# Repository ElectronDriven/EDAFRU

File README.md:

# EDAFRU
Electron Driven Air to Fuel Ratio Measurement Unit

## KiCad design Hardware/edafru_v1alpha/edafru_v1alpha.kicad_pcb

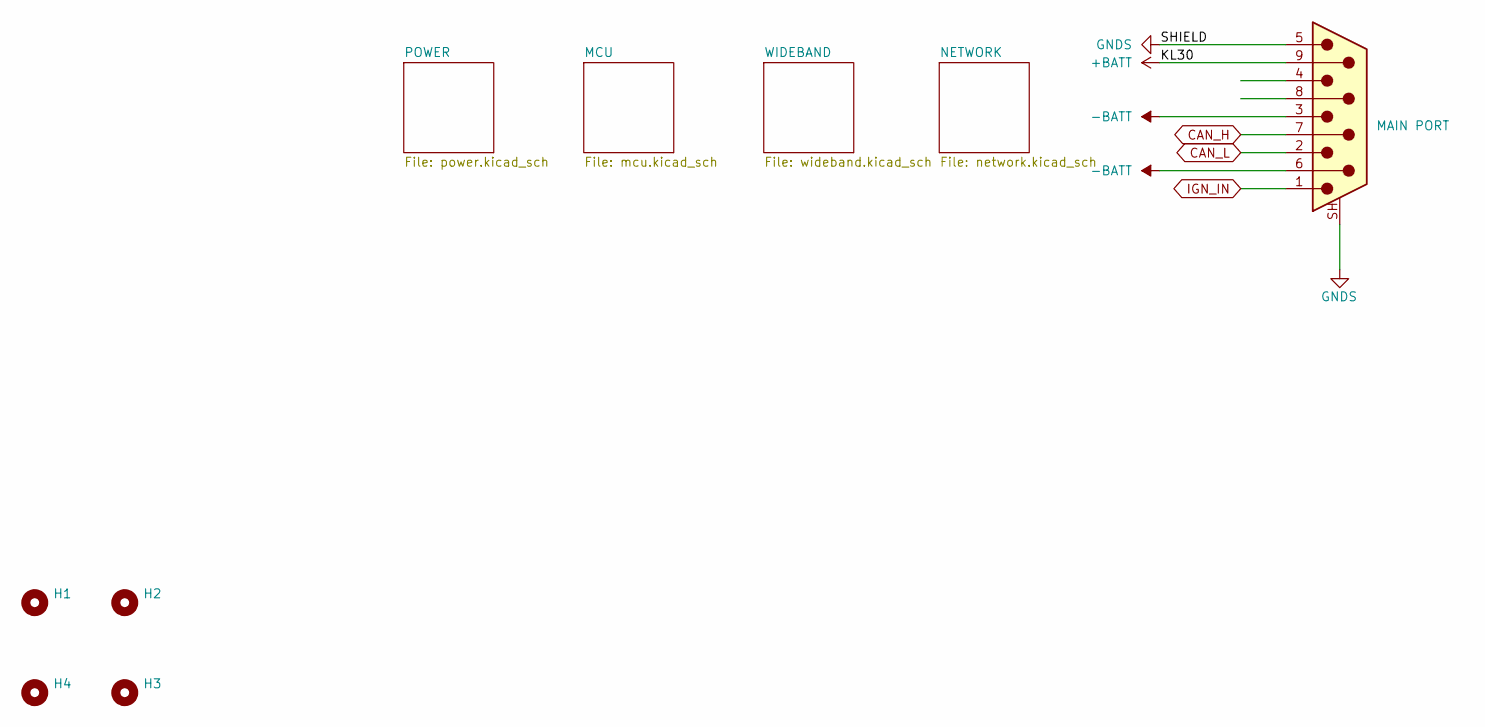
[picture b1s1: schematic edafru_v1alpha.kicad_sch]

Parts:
H1, H2, H3, H4: MountingHole; MountingHole_3.2mm_M3_DIN965
J2: MAIN PORT; DSUB-9_Pins_Horizontal_P2.77x2.84mm_EdgePinOffset4.94mm_Hou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

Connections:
+BATT: J2.9; also elsewhere on the board
-BATT: J2.3, J2.6; also elsewhere on the board
CAN_H: J2.7; also elsewhere on the board
CAN_L: J2.2; also elsewhere on the board
GNDS: J2.5, J2.SH (PAD)
IGN_IN: J2.1; also elsewhere on the board

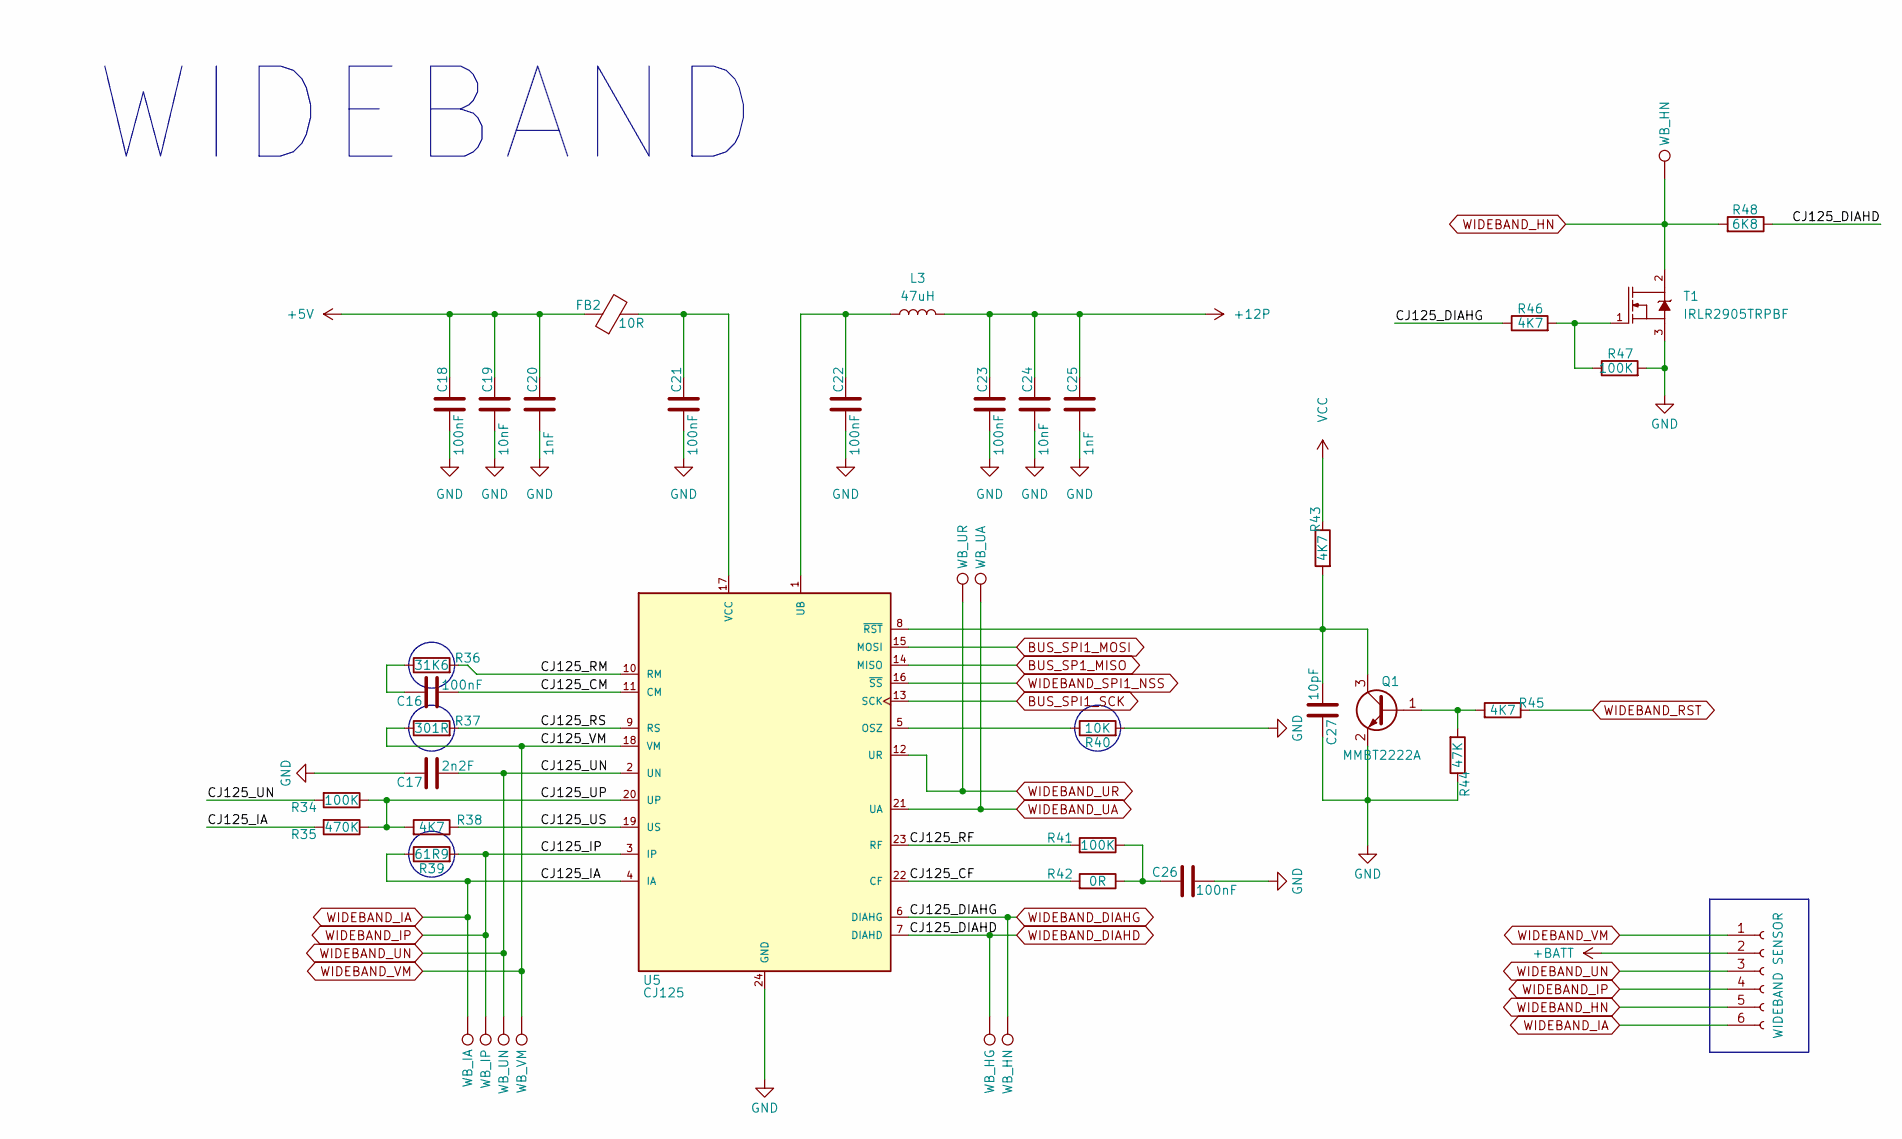
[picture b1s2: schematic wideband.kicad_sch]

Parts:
C16, C26: 100nF; C_0603_1608Metric_Pad1.08x0.95mm_HandSolder
C17: 2n2F; C_0603_1608Metric_Pad1.08x0.95mm_HandSolder
C18, C21, C22, C23: 100nF; C_1206_3216Metric_Pad1.33x1.80mm_HandSolder
C19, C24: 10nF; C_1206_3216Metric_Pad1.33x1.80mm_HandSolder
C20, C25: 1nF; C_1206_3216Metric_Pad1.33x1.80mm_HandSolder
C27: 10pF; C_0603_1608Metric_Pad1.08x0.95mm_HandSolder
FB2: 10R; L_1206_3216Metric_Pad1.22x1.90mm_HandSolder
J4: WIDEBAND SENSOR; Molex_KK-254_AE-6410-06A_1x06_P2.54mm_Vertical
L3: 47uH; L_1210_3225Metric_Pad1.42x2.65mm_HandSolder
Q1: MMBT2222A; SOT-23
R34, R41: 100K; R_0603_1608Metric_Pad0.98x0.95mm_HandSolder
R35: 470K; R_0603_1608Metric_Pad0.98x0.95mm_HandSolder
R36: 31K6; R_MELF_MMB-0207
R37: 301R; R_MELF_MMB-0207
R38, R43, R45: 4K7; R_0603_1608Metric_Pad0.98x0.95mm_HandSolder
R39: 61R9; R_MELF_MMB-0207
R40: 10K; R_MELF_MMB-0207
R42: 0R; R_0603_1608Metric_Pad0.98x0.95mm_HandSolder
R44: 47K; R_0603_1608Metric_Pad0.98x0.95mm_HandSolder
R46: 4K7; R_1206_3216Metric_Pad1.30x1.75mm_HandSolder
R47: 100K; R_1206_3216Metric_Pad1.30x1.75mm_HandSolder
R48: 6K8; R_1206_3216Metric_Pad1.30x1.75mm_HandSolder
T1: IRLR2905TRPBF
TP1: WB_IA; TestPoint_Pad_D1.0mm
TP2: WB_IP; TestPoint_Pad_D1.0mm
TP3: WB_UN; TestPoint_Pad_D1.0mm
TP4: WB_VM; TestPoint_Pad_D1.0mm
TP5: WB_UR; TestPoint_Pad_D1.0mm
TP6: WB_UA; TestPoint_Pad_D1.0mm
TP7: WB_HG; TestPoint_Pad_D1.0mm
TP8, TP9: WB_HN; TestPoint_Pad_D1.0mm
U5: CJ125; SOIC-24W_7.5x15.4mm_P1.27mm

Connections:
+5V: C18.1, C19.1, C20.1, FB2.1; also elsewhere on the board
+12P: C23.1, C24.1, C25.1, L3.2; also elsewhere on the board
+BATT: J4.2; also elsewhere on the board
/WIDEBAND/CJ125_CF: R42.2, U5.22 (CF)
/WIDEBAND/CJ125_CM: C16.1, U5.11 (CM)
/WIDEBAND/CJ125_RF: R41.2, U5.23 (RF)
/WIDEBAND/CJ125_RM: R36.2, U5.10 (RM)
/WIDEBAND/CJ125_RS: R37.2, U5.9 (RS)
/WIDEBAND/CJ125_UP: R34.1, R35.1, R38.2, U5.20 (UP)
/WIDEBAND/CJ125_US: R38.1, U5.19 (US)
BUS_SP1_MISO: U5.14 (MISO); also elsewhere on the board
BUS_SPI1_MOSI: U5.15 (MOSI); also elsewhere on the board
BUS_SPI1_SCK: U5.13 (SCK); also elsewhere on the board
GND: C17.2, C18.2, C19.2, C20.2, C21.2, C22.2, C23.2, C24.2, C25.2, C26.2, C27.2, Q1.2 (E), R40.2, R44.1, R47.2, T1.3, U5.24 (GND); also elsewhere on the board
unnamed: C16.2, R36.1
unnamed: C26.1, R41.1, R42.1
unnamed: Q1.1 (B), R44.2, R45.2
unnamed: C27.1, Q1.3 (C), R43.2, U5.8 (~RST)
unnamed: R46.2, R47.1, T1.1
unnamed: R40.1, U5.5 (OSZ)
unnamed: C22.1, L3.1, U5.1 (UB)
unnamed: C21.1, FB2.2, U5.17 (VCC)
VCC: R43.1; also elsewhere on the board
WIDEBAND_DIAHD: R48.1, TP7.1 (1_1), U5.7 (DIAHD); also elsewhere on the board
WIDEBAND_DIAHG: R46.1, TP8.1 (1_1), U5.6 (DIAHG); also elsewhere on the board
WIDEBAND_HN: J4.5, R48.2, T1.2, T1.PAD, TP9.1 (1_1)
WIDEBAND_IA: J4.6, R35.2, R39.1, TP1.1 (1_1), U5.4 (IA)
WIDEBAND_IP: J4.4, R39.2, TP2.1 (1_1), U5.3 (IP)
WIDEBAND_RST: R45.1; also elsewhere on the board
WIDEBAND_SPI1_NSS: U5.16 (~SS); also elsewhere on the board
WIDEBAND_UA: TP6.1 (1_1), U5.21 (UA); also elsewhere on the board
WIDEBAND_UN: C17.1, J4.3, R34.2, TP3.1 (1_1), U5.2 (UN)
WIDEBAND_UR: TP5.1 (1_1), U5.12 (UR); also elsewhere on the board
WIDEBAND_VM: J4.1, R37.1, TP4.1 (1_1), U5.18 (VM)

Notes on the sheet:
WIDEBAND

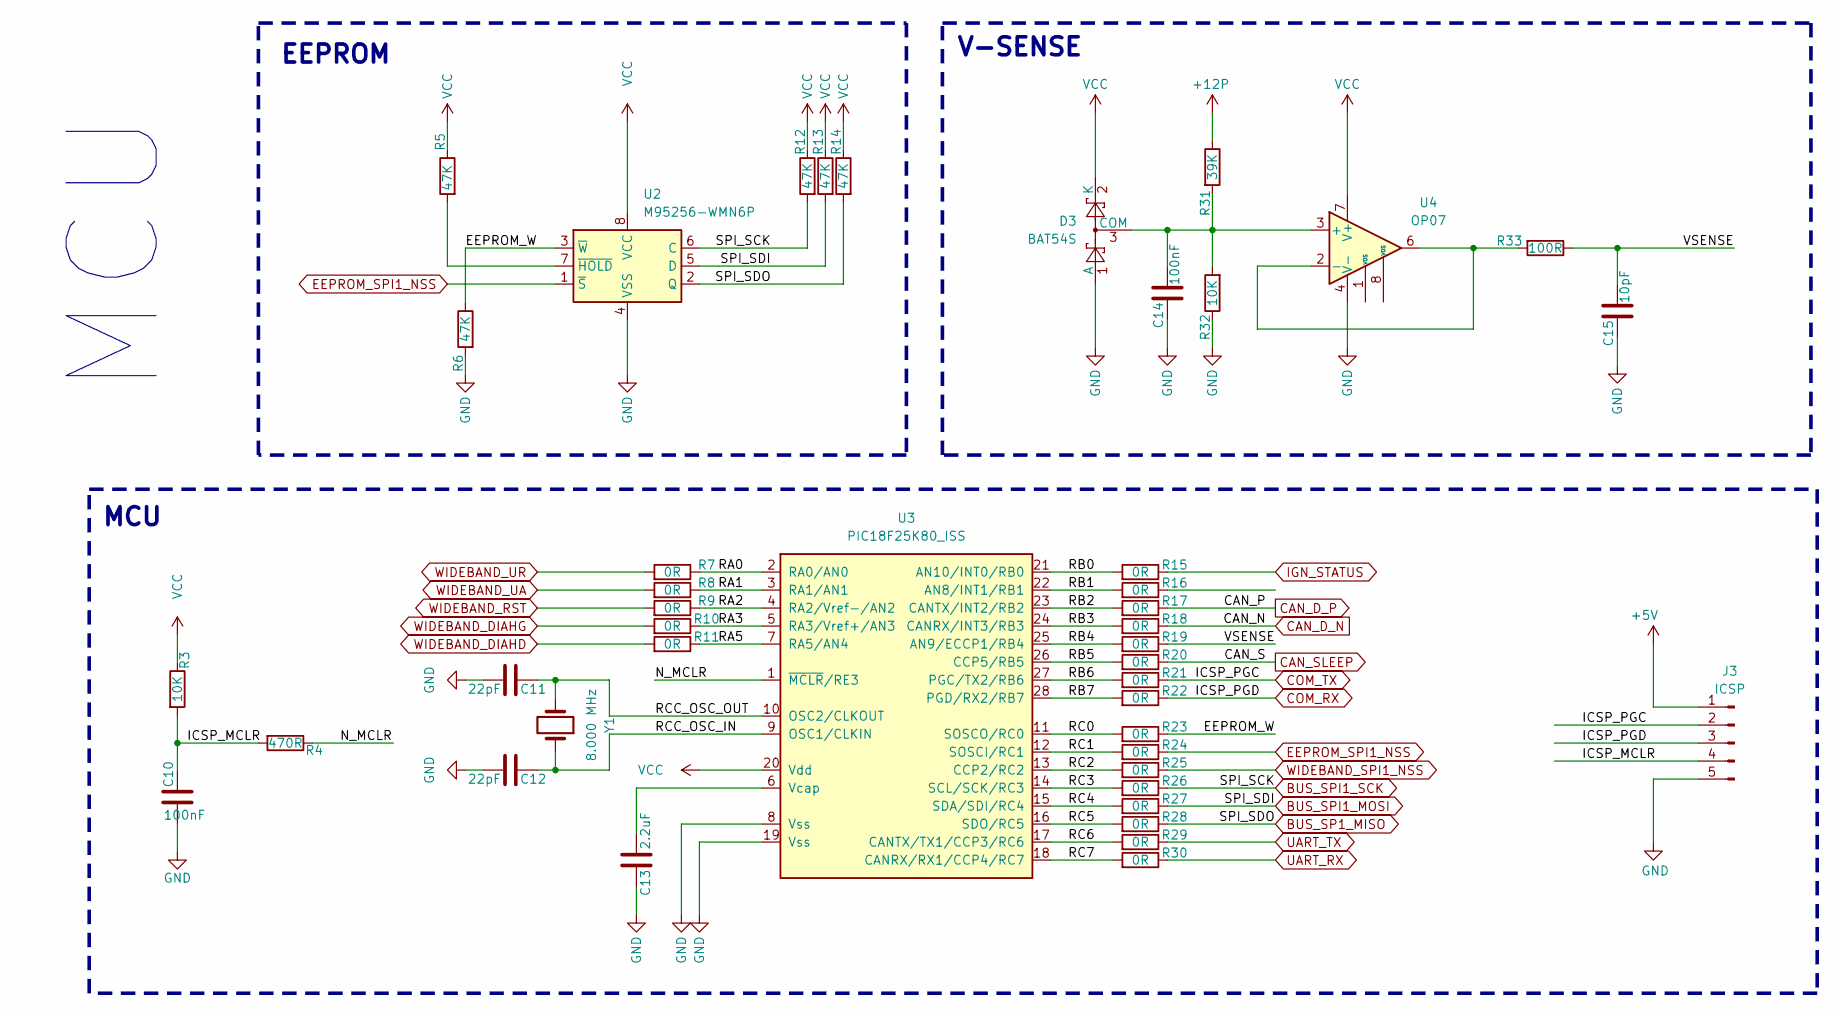
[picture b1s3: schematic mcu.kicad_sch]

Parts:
C10, C14: 100nF; C_0603_1608Metric_Pad1.08x0.95mm_HandSolder
C11, C12: 22pF; C_0603_1608Metric_Pad1.08x0.95mm_HandSolder
C13: 2.2uF; C_0603_1608Metric_Pad1.08x0.95mm_HandSolder
C15: 10pF; C_0603_1608Metric_Pad1.08x0.95mm_HandSolder
D3: BAT54S; SOT-23
J3: ICSP; PinHeader_1x05_P2.54mm_Vertical
R3, R32: 10K; R_0603_1608Metric_Pad0.98x0.95mm_HandSolder
R4: 470R; R_0603_1608Metric_Pad0.98x0.95mm_HandSolder
R5, R6, R12, R13, R14: 47K; R_0603_1608Metric_Pad0.98x0.95mm_HandSolder
R7, R8, R9, R10, R11, R15, R16, R17, R18, R19, R20, R21, R22, R23, R24, R25, R26, R27, R28, R29, R30: 0R; R_0603_1608Metric_Pad0.98x0.95mm_HandSolder
R31: 39K; R_0603_1608Metric_Pad0.98x0.95mm_HandSolder
R33: 100R; R_0603_1608Metric_Pad0.98x0.95mm_HandSolder
U2: M95256-WMN6P; SOIC-8_3.9x4.9mm_P1.27mm
U3: PIC18F25K80_ISS; SSOP-28_5.3x10.2mm_P0.65mm
U4: OP07; SOIC-8_3.9x4.9mm_P1.27mm
Y1: 8.000 MHz; Crystal_SMD_5032-2Pin_5.0x3.2mm_HandSoldering

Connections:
+5V: J3.1; also elsewhere on the board
+12P: R31.1; also elsewhere on the board
/MCU/EEPROM_W: R6.1, R23.1, U2.3 (~W)
/MCU/ICSP_MCLR: C10.1, J3.4, R3.2, R4.2
/MCU/N_MCLR: R4.1, U3.1 (~MCLR/RE3)
/MCU/RA0: R7.1, U3.2 (RA0/AN0)
/MCU/RA1: R8.1, U3.3 (RA1/AN1)
/MCU/RA2: R9.1, U3.4 (RA2/Vref-/AN2)
/MCU/RA3: R10.1, U3.5 (RA3/Vref+/AN3)
/MCU/RA5: R11.1, U3.7 (RA5/AN4)
/MCU/RB0: R15.2, U3.21 (AN10/INT0/RB0)
/MCU/RB1: R16.2, U3.22 (AN8/INT1/RB1)
/MCU/RB2: R17.2, U3.23 (CANTX/INT2/RB2)
/MCU/RB3: R18.2, U3.24 (CANRX/INT3/RB3)
/MCU/RB4: R19.2, U3.25 (AN9/ECCP1/RB4)
/MCU/RB5: R20.2, U3.26 (CCP5/RB5)
/MCU/RB6: R21.2, U3.27 (PGC/TX2/RB6)
/MCU/RB7: R22.2, U3.28 (PGD/RX2/RB7)
/MCU/RC0: R23.2, U3.11 (SOSCO/RC0)
/MCU/RC1: R24.2, U3.12 (SOSCI/RC1)
/MCU/RC2: R25.2, U3.13 (CCP2/RC2)
/MCU/RC3: R26.2, U3.14 (SCL/SCK/RC3)
/MCU/RC4: R27.2, U3.15 (SDA/SDI/RC4)
/MCU/RC5: R28.2, U3.16 (SDO/RC5)
/MCU/RC6: R29.2, U3.17 (CANTX/TX1/CCP3/RC6)
/MCU/RC7: R30.2, U3.18 (CANRX/RX1/CCP4/RC7)
/MCU/RCC_OSC_IN: C12.1, U3.9 (OSC1/CLKIN), Y1.1
/MCU/RCC_OSC_OUT: C11.1, U3.10 (OSC2/CLKOUT), Y1.2
/MCU/VSENSE: C15.1, R19.1, R33.1
BUS_SP1_MISO: R14.2, R28.1, U2.2 (Q); also elsewhere on the board
BUS_SPI1_MOSI: R13.2, R27.1, U2.5 (D); also elsewhere on the board
BUS_SPI1_SCK: R12.2, R26.1, U2.6 (C); also elsewhere on the board
CAN_D_N: R18.1; also elsewhere on the board
CAN_D_P: R17.1; also elsewhere on the board
CAN_SLEEP: R20.1; also elsewhere on the board
COM_RX: J3.3, R22.1
COM_TX: J3.2, R21.1
EEPROM_SPI1_NSS: R24.1, U2.1 (~S)
GND: C10.2, C11.2, C12.2, C13.1, C14.2, C15.2, D3.1 (A), J3.5, R6.2, R32.1, U2.4 (VSS), U3.8 (Vss), U3.19 (Vss), U4.4 (V-); also elsewhere on the board
IGN_STATUS: R15.1; also elsewhere on the board
unnamed: C14.1, D3.3 (COM), R31.2, R32.2, U4.3 (+)
unnamed: R5.2, U2.7 (~HOLD)
unnamed: C13.2, U3.6 (Vcap)
unnamed: R33.2, U4.2 (-), U4.6
UART_RX: R30.1
UART_TX: R29.1
VCC: D3.2 (K), R3.1, R5.1, R12.1, R13.1, R14.1, U2.8 (VCC), U3.20 (Vdd), U4.7 (V+); also elsewhere on the board
WIDEBAND_DIAHD: R11.2; also elsewhere on the board
WIDEBAND_DIAHG: R10.2; also elsewhere on the board
WIDEBAND_RST: R9.2; also elsewhere on the board
WIDEBAND_SPI1_NSS: R25.1; also elsewhere on the board
WIDEBAND_UA: R8.2; also elsewhere on the board
WIDEBAND_UR: R7.2; also elsewhere on the board

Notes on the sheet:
EEPROM
V-SENSE
MCU
MCU

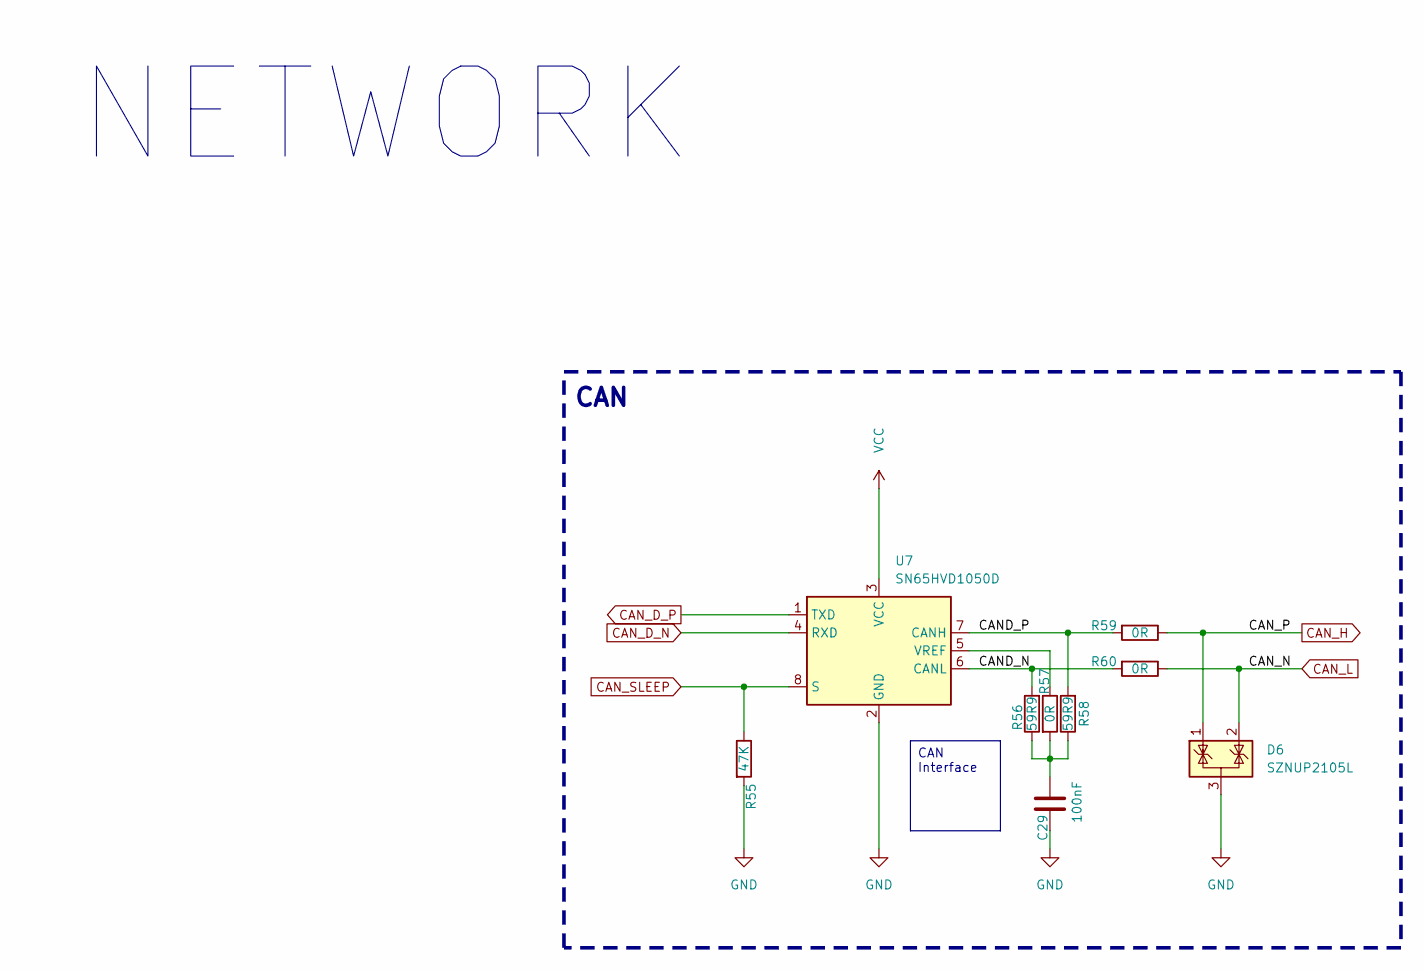
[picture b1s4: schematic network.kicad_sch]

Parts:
C29: 100nF; C_0603_1608Metric_Pad1.08x0.95mm_HandSolder
D6: SZNUP2105L; SOT-23
R55: 47K; R_0603_1608Metric_Pad0.98x0.95mm_HandSolder
R56, R58: 59R9; R_0603_1608Metric_Pad0.98x0.95mm_HandSolder
R57, R59, R60: 0R; R_0603_1608Metric_Pad0.98x0.95mm_HandSolder
U7: SN65HVD1050D; SOIC-8_3.9x4.9mm_P1.27mm

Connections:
/NETWORK/CAND_N: R56.2, R60.2, U7.6 (CANL)
/NETWORK/CAND_P: R58.2, R59.2, U7.7 (CANH)
CAN_D_N: U7.4 (RXD); also elsewhere on the board
CAN_D_P: U7.1 (TXD); also elsewhere on the board
CAN_H: D6.1 (K), R59.1; also elsewhere on the board
CAN_L: D6.2 (K), R60.1; also elsewhere on the board
CAN_SLEEP: R55.1, U7.8 (S); also elsewhere on the board
GND: C29.2, D6.3 (A), R55.2, U7.2 (GND); also elsewhere on the board
unnamed: C29.1, R56.1, R57.2, R58.1
unnamed: R57.1, U7.5 (VREF)
VCC: U7.3 (VCC); also elsewhere on the board

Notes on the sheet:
CAN
NETWORK
CAN Interface

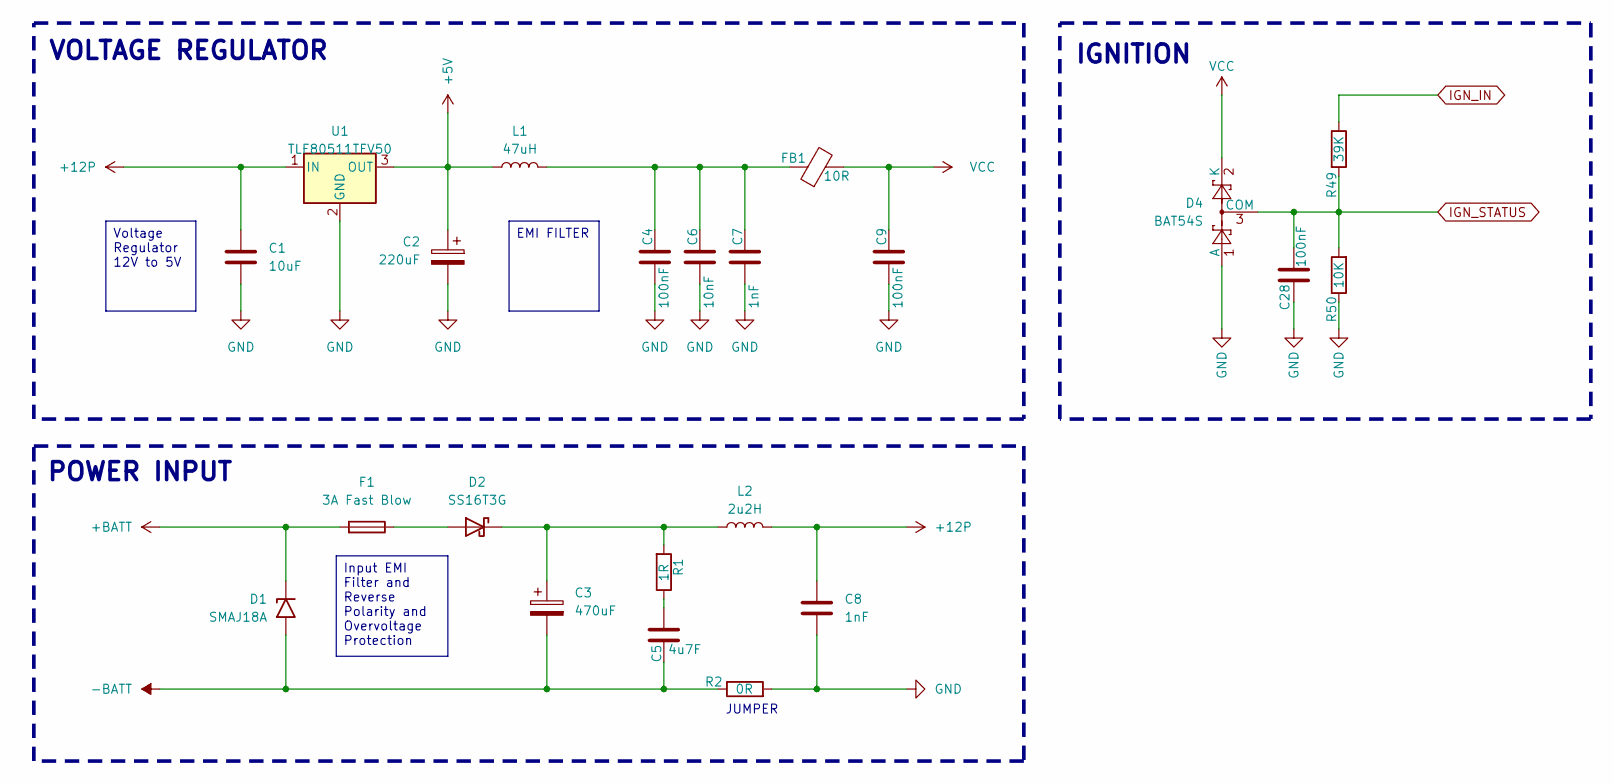
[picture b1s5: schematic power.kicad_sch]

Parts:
C1: 10uF; C_1206_3216Metric_Pad1.33x1.80mm_HandSolder
C2: 220uF; CP_EIA-7343-30_AVX-N
C3: 470uF; CP_Elec_10x10
C4, C9: 100nF; C_1206_3216Metric_Pad1.33x1.80mm_HandSolder
C5: 4u7F; C_1206_3216Metric_Pad1.33x1.80mm_HandSolder
C6: 10nF; C_1206_3216Metric_Pad1.33x1.80mm_HandSolder
C7, C8: 1nF; C_1206_3216Metric_Pad1.33x1.80mm_HandSolder
C28: 100nF; C_0603_1608Metric_Pad1.08x0.95mm_HandSolder
D1: SMAJ18A; D_SMA
D2: SS16T3G; D_SMA
D4: BAT54S; SOT-23
F1: 3A Fast Blow; Fuse_1206_3216Metric_Pad1.42x1.75mm_HandSolder
FB1: 10R; L_1206_3216Metric_Pad1.22x1.90mm_HandSolder
L1: 47uH; L_1210_3225Metric_Pad1.42x2.65mm_HandSolder
L2: 2u2H; L_1210_3225Metric_Pad1.42x2.65mm_HandSolder
R1: 1R; R_1206_3216Metric_Pad1.30x1.75mm_HandSolder
R2: 0R; R_1206_3216Metric_Pad1.30x1.75mm_HandSolder
R49: 39K; R_0603_1608Metric_Pad0.98x0.95mm_HandSolder
R50: 10K; R_0603_1608Metric_Pad0.98x0.95mm_HandSolder
U1: TLF80511TFV50; TO-252-2

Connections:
+5V: C2.1, L1.1, U1.3 (OUT); also elsewhere on the board
+12P: C1.1, C8.1, L2.2, U1.1 (IN); also elsewhere on the board
+BATT: D1.1 (A1), F1.2; also elsewhere on the board
-BATT: C3.2, C5.1, D1.2 (A2), R2.1; also elsewhere on the board
GND: C1.2, C2.2, C4.2, C6.2, C7.2, C8.2, C9.2, C28.2, D4.1 (A), R2.2, R50.1, U1.2 (GND); also elsewhere on the board
IGN_IN: R49.1; also elsewhere on the board
IGN_STATUS: C28.1, D4.3 (COM), R49.2, R50.2; also elsewhere on the board
unnamed: C4.1, C6.1, C7.1, FB1.1, L1.2
unnamed: C5.2, R1.1
unnamed: D2.2 (A), F1.1
unnamed: C3.1, D2.1 (K), L2.1, R1.2
VCC: C9.1, D4.2 (K), FB1.2; also elsewhere on the board

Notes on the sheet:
IGNITION
JUMPER
VOLTAGE REGULATOR
POWER INPUT
Input EMI Filter and Reverse Polarity and Overvoltage Protection
Voltage Regulator 12V to 5V
EMI FILTER

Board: 2 copper layers, 121 parts (9 on the bottom side), 85 nets, no tracks yet.

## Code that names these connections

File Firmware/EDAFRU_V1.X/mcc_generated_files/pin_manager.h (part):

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// get/set WIDEBAND_UR aliases
#define WIDEBAND_UR_TRIS                 TRISAbits.TRISA0
#define WIDEBAND_UR_LAT                  LATAbits.LATA0
#define WIDEBAND_UR_PORT                 PORTAbits.RA0
#define WIDEBAND_UR_ANS                  ANCON0bits.ANSEL0
#define WIDEBAND_UR_SetHigh()            do { LATAbits.LATA0 = 1; } while(0)
#define WIDEBAND_UR_SetLow()             do { LATAbits.LATA0 = 0; } while(0)
#define WIDEBAND_UR_Toggle()             do { LATAbits.LATA0 = ~LATAbits.LATA0; } while(0)
#define WIDEBAND_UR_GetValue()           PORTAbits.RA0
#define WIDEBAND_UR_SetDigitalInput()    do { TRISAbits.TRISA0 = 1; } while(0)
#define WIDEBAND_UR_SetDigitalOutput()   do { TRISAbits.TRISA0 = 0; } while(0)
#define WIDEBAND_UR_SetAnalogMode()      do { ANCON0bits.ANSEL0 = 1; } while(0)
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// get/set WIDEBAND_UA aliases
#define WIDEBAND_UA_TRIS                 TRISAbits.TRISA1
#define WIDEBAND_UA_LAT                  LATAbits.LATA1
#define WIDEBAND_UA_PORT                 PORTAbits.RA1
#define WIDEBAND_UA_ANS                  ANCON0bits.ANSEL1
#define WIDEBAND_UA_SetHigh()            do { LATAbits.LATA1 = 1; } while(0)
#define WIDEBAND_UA_SetLow()             do { LATAbits.LATA1 = 0; } while(0)
#define WIDEBAND_UA_Toggle()             do { LATAbits.LATA1 = ~LATAbits.LATA1; } while(0)
#define WIDEBAND_UA_GetValue()           PORTAbits.RA1
#define WIDEBAND_UA_SetDigitalInput()    do { TRISAbits.TRISA1 = 1; } while(0)
#define WIDEBAND_UA_SetDigitalOutput()   do { TRISAbits.TRISA1 = 0; } while(0)
#define WIDEBAND_UA_SetAnalogMode()      do { ANCON0bits.ANSEL1 = 1; } while(0)
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// get/set VSENSE aliases
#define VSENSE_TRIS                 TRISAbits.TRISA5
#define VSENSE_LAT                  LATAbits.LATA5
#define VSENSE_PORT                 PORTAbits.RA5
#define VSENSE_ANS                  ANCON0bits.ANSEL4
#define VSENSE_SetHigh()            do { LATAbits.LATA5 = 1; } while(0)
#define VSENSE_SetLow()             do { LATAbits.LATA5 = 0; } while(0)
#define VSENSE_Toggle()             do { LATAbits.LATA5 = ~LATAbits.LATA5; } while(0)
#define VSENSE_GetValue()           PORTAbits.RA5
#define VSENSE_SetDigitalInput()    do { TRISAbits.TRISA5 = 1; } while(0)
#define VSENSE_SetDigitalOutput()   do { TRISAbits.TRISA5 = 0; } while(0)
#define VSENSE_SetAnalogMode()      do { ANCON0bits.ANSEL4 = 1; } while(0)
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#define RB2_SetHigh()            do { LATBbits.LATB2 = 1; } while(0)
#define RB2_SetLow()             do { LATBbits.LATB2 = 0; } while(0)
#define RB2_Toggle()             do { LATBbits.LATB2 = ~LATBbits.LATB2; } while(0)
#define RB2_GetValue()              PORTBbits.RB2
#define RB2_SetDigitalInput()    do { TRISBbits.TRISB2 = 1; } while(0)
#define RB2_SetDigitalOutput()   do { TRISBbits.TRISB2 = 0; } while(0)
#define RB2_SetPullup()             do { WPUBbits.WPUB2 = 1; } while(0)
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#define RB3_SetHigh()            do { LATBbits.LATB3 = 1; } while(0)
#define RB3_SetLow()             do { LATBbits.LATB3 = 0; } while(0)
#define RB3_Toggle()             do { LATBbits.LATB3 = ~LATBbits.LATB3; } while(0)
#define RB3_GetValue()              PORTBbits.RB3
#define RB3_SetDigitalInput()    do { TRISBbits.TRISB3 = 1; } while(0)
#define RB3_SetDigitalOutput()   do { TRISBbits.TRISB3 = 0; } while(0)
#define RB3_SetPullup()             do { WPUBbits.WPUB3 = 1; } while(0)
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// get/set CAN_SLEEP aliases
#define CAN_SLEEP_TRIS                 TRISBbits.TRISB4
#define CAN_SLEEP_LAT                  LATBbits.LATB4
#define CAN_SLEEP_PORT                 PORTBbits.RB4
#define CAN_SLEEP_WPU                  WPUBbits.WPUB4
#define CAN_SLEEP_ANS                  ANCON1bits.ANSEL9
#define CAN_SLEEP_SetHigh()            do { LATBbits.LATB4 = 1; } while(0)
#define CAN_SLEEP_SetLow()             do { LATBbits.LATB4 = 0; } while(0)
#define CAN_SLEEP_Toggle()             do { LATBbits.LATB4 = ~LATBbits.LATB4; } while(0)
#define CAN_SLEEP_GetValue()           PORTBbits.RB4
#define CAN_SLEEP_SetDigitalInput()    do { TRISBbits.TRISB4 = 1; } while(0)
#define CAN_SLEEP_SetDigitalOutput()   do { TRISBbits.TRISB4 = 0; } while(0)
#define CAN_SLEEP_SetPullup()          do { WPUBbits.WPUB4 = 1; } while(0)
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// get/set LIN_SLEEP aliases
#define LIN_SLEEP_TRIS                 TRISBbits.TRISB5
#define LIN_SLEEP_LAT                  LATBbits.LATB5
#define LIN_SLEEP_PORT                 PORTBbits.RB5
#define LIN_SLEEP_WPU                  WPUBbits.WPUB5
#define LIN_SLEEP_SetHigh()            do { LATBbits.LATB5 = 1; } while(0)
#define LIN_SLEEP_SetLow()             do { LATBbits.LATB5 = 0; } while(0)
#define LIN_SLEEP_Toggle()             do { LATBbits.LATB5 = ~LATBbits.LATB5; } while(0)
#define LIN_SLEEP_GetValue()           PORTBbits.RB5
#define LIN_SLEEP_SetDigitalInput()    do { TRISBbits.TRISB5 = 1; } while(0)
#define LIN_SLEEP_SetDigitalOutput()   do { TRISBbits.TRISB5 = 0; } while(0)
#define LIN_SLEEP_SetPullup()          do { WPUBbits.WPUB5 = 1; } while(0)
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#define RB6_SetHigh()            do { LATBbits.LATB6 = 1; } while(0)
#define RB6_SetLow()             do { LATBbits.LATB6 = 0; } while(0)
#define RB6_Toggle()             do { LATBbits.LATB6 = ~LATBbits.LATB6; } while(0)
#define RB6_GetValue()              PORTBbits.RB6
#define RB6_SetDigitalInput()    do { TRISBbits.TRISB6 = 1; } while(0)
#define RB6_SetDigitalOutput()   do { TRISBbits.TRISB6 = 0; } while(0)
#define RB6_SetPullup()             do { WPUBbits.WPUB6 = 1; } while(0)
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#define RB7_SetHigh()            do { LATBbits.LATB7 = 1; } while(0)
#define RB7_SetLow()             do { LATBbits.LATB7 = 0; } while(0)
#define RB7_Toggle()             do { LATBbits.LATB7 = ~LATBbits.LATB7; } while(0)
#define RB7_GetValue()              PORTBbits.RB7
#define RB7_SetDigitalInput()    do { TRISBbits.TRISB7 = 1; } while(0)
#define RB7_SetDigitalOutput()   do { TRISBbits.TRISB7 = 0; } while(0)
#define RB7_SetPullup()             do { WPUBbits.WPUB7 = 1; } while(0)
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// get/set EEPROM_W aliases
#define EEPROM_W_TRIS                 TRISCbits.TRISC0
#define EEPROM_W_LAT                  LATCbits.LATC0
#define EEPROM_W_PORT                 PORTCbits.RC0
#define EEPROM_W_SetHigh()            do { LATCbits.LATC0 = 1; } while(0)
#define EEPROM_W_SetLow()             do { LATCbits.LATC0 = 0; } while(0)
#define EEPROM_W_Toggle()             do { LATCbits.LATC0 = ~LATCbits.LATC0; } while(0)
#define EEPROM_W_GetValue()           PORTCbits.RC0
#define EEPROM_W_SetDigitalInput()    do { TRISCbits.TRISC0 = 1; } while(0)
#define EEPROM_W_SetDigitalOutput()   do { TRISCbits.TRISC0 = 0; } while(0)

// get/set EEPROM_S aliases
#define EEPROM_S_TRIS                 TRISCbits.TRISC1
#define EEPROM_S_LAT                  LATCbits.LATC1
#define EEPROM_S_PORT                 PORTCbits.RC1
#define EEPROM_S_SetHigh()            do { LATCbits.LATC1 = 1; } while(0)
#define EEPROM_S_SetLow()             do { LATCbits.LATC1 = 0; } while(0)
#define EEPROM_S_Toggle()             do { LATCbits.LATC1 = ~LATCbits.LATC1; } while(0)
#define EEPROM_S_GetValue()           PORTCbits.RC1
#define EEPROM_S_SetDigitalInput()    do { TRISCbits.TRISC1 = 1; } while(0)
#define EEPROM_S_SetDigitalOutput()   do { TRISCbits.TRISC1 = 0; } while(0)

// get/set WIDEBAND_SPI1_NSS aliases
#define WIDEBAND_SPI1_NSS_TRIS                 TRISCbits.TRISC2
#define WIDEBAND_SPI1_NSS_LAT                  LATCbits.LATC2
#define WIDEBAND_SPI1_NSS_PORT                 PORTCbits.RC2
#define WIDEBAND_SPI1_NSS_SetHigh()            do { LATCbits.LATC2 = 1; } while(0)
#define WIDEBAND_SPI1_NSS_SetLow()             do { LATCbits.LATC2 = 0; } while(0)
#define WIDEBAND_SPI1_NSS_Toggle()             do { LATCbits.LATC2 = ~LATCbits.LATC2; } while(0)
#define WIDEBAND_SPI1_NSS_GetValue()           PORTCbits.RC2
#define WIDEBAND_SPI1_NSS_SetDigitalInput()    do { TRISCbits.TRISC2 = 1; } while(0)
#define WIDEBAND_SPI1_NSS_SetDigitalOutput()   do { TRISCbits.TRISC2 = 0; } while(0)

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#define RC3_SetHigh()            do { LATCbits.LATC3 = 1; } while(0)
#define RC3_SetLow()             do { LATCbits.LATC3 = 0; } while(0)
#define RC3_Toggle()             do { LATCbits.LATC3 = ~LATCbits.LATC3; } while(0)
#define RC3_GetValue()              PORTCbits.RC3
#define RC3_SetDigitalInput()    do { TRISCbits.TRISC3 = 1; } while(0)
#define RC3_SetDigitalOutput()   do { TRISCbits.TRISC3 = 0; } while(0)

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#define RC4_SetHigh()            do { LATCbits.LATC4 = 1; } while(0)
#define RC4_SetLow()             do { LATCbits.LATC4 = 0; } while(0)
#define RC4_Toggle()             do { LATCbits.LATC4 = ~LATCbits.LATC4; } while(0)
#define RC4_GetValue()              PORTCbits.RC4
#define RC4_SetDigitalInput()    do { TRISCbits.TRISC4 = 1; } while(0)
#define RC4_SetDigitalOutput()   do { TRISCbits.TRISC4 = 0; } while(0)

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#define RC5_SetHigh()            do { LATCbits.LATC5 = 1; } while(0)
#define RC5_SetLow()             do { LATCbits.LATC5 = 0; } while(0)
#define RC5_Toggle()             do { LATCbits.LATC5 = ~LATCbits.LATC5; } while(0)
#define RC5_GetValue()              PORTCbits.RC5
#define RC5_SetDigitalInput()    do { TRISCbits.TRISC5 = 1; } while(0)
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
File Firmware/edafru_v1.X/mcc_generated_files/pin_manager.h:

/**
  @Generated Pin Manager Header File

  @Company:
    Microchip Technology Inc.

  @File Name:
    pin_manager.h

  @Summary:
    This is the Pin Manager file generated using PIC10 / PIC12 / PIC16 / PIC18 MCUs

  @Description
    This header file provides APIs for driver for .
    Generation Information :
        Product Revision  :  PIC10 / PIC12 / PIC16 / PIC18 MCUs - 1.81.8
        Device            :  PIC18F25K80
        Driver Version    :  2.11
    The generated drivers are tested against the following:
        Compiler          :  XC8 2.36 and above
        MPLAB 	          :  MPLAB X 6.00	
*/

/*
    (c) 2018 Microchip Technology Inc. and its subsidiaries. 
    
    Subject to your compliance with these terms, you may use Microchip software and any 
    derivatives exclusively with Microchip products. It is your responsibility to comply with third party 
    license terms applicable to your use of third party software (including open source software) that 
    may accompany Microchip software.
    
    THIS SOFTWARE IS SUPPLIED BY MICROCHIP "AS IS". NO WARRANTIES, WHETHER 
    EXPRESS, IMPLIED OR STATUTORY, APPLY TO THIS SOFTWARE, INCLUDING ANY 
    IMPLIED WARRANTIES OF NON-INFRINGEMENT, MERCHANTABILITY, AND FITNESS 
    FOR A PARTICULAR PURPOSE.
    
    IN NO EVENT WILL MICROCHIP BE LIABLE FOR ANY INDIRECT, SPECIAL, PUNITIVE, 
    INCIDENTAL OR CONSEQUENTIAL LOSS, DAMAGE, COST OR EXPENSE OF ANY KIND 
    WHATSOEVER RELATED TO THE SOFTWARE, HOWEVER CAUSED, EVEN IF MICROCHIP 
    HAS BEEN ADVISED OF THE POSSIBILITY OR THE DAMAGES ARE FORESEEABLE. TO 
    THE FULLEST EXTENT ALLOWED BY LAW, MICROCHIP'S TOTAL LIABILITY ON ALL 
    CLAIMS IN ANY WAY RELATED TO THIS SOFTWARE WILL NOT EXCEED THE AMOUNT 
    OF FEES, IF ANY, THAT YOU HAVE PAID DIRECTLY TO MICROCHIP FOR THIS 
    SOFTWARE.
*/

#ifndef PIN_MANAGER_H
#define PIN_MANAGER_H

/**
  Section: Included Files
*/

#include <xc.h>

#define INPUT   1
#define OUTPUT  0

#define HIGH    1
#define LOW     0

#define ANALOG      1
#define DIGITAL     0

#define PULL_UP_ENABLED      1
#define PULL_UP_DISABLED     0

// get/set channel_AN0 aliases
#define channel_AN0_TRIS                 TRISAbits.TRISA0
#define channel_AN0_LAT                  LATAbits.LATA0
#define channel_AN0_PORT                 PORTAbits.RA0
#define channel_AN0_ANS                  ANCON0bits.ANSEL0
#define channel_AN0_SetHigh()            do { LATAbits.LATA0 = 1; } while(0)
#define channel_AN0_SetLow()             do { LATAbits.LATA0 = 0; } while(0)
#define channel_AN0_Toggle()             do { LATAbits.LATA0 = ~LATAbits.LATA0; } while(0)
#define channel_AN0_GetValue()           PORTAbits.RA0
#define channel_AN0_SetDigitalInput()    do { TRISAbits.TRISA0 = 1; } while(0)
#define channel_AN0_SetDigitalOutput()   do { TRISAbits.TRISA0 = 0; } while(0)
#define channel_AN0_SetAnalogMode()      do { ANCON0bits.ANSEL0 = 1; } while(0)
#define channel_AN0_SetDigitalMode()     do { ANCON0bits.ANSEL0 = 0; } while(0)

// get/set channel_AN1 aliases
#define channel_AN1_TRIS                 TRISAbits.TRISA1
#define channel_AN1_LAT                  LATAbits.LATA1
#define channel_AN1_PORT                 PORTAbits.RA1
#define channel_AN1_ANS                  ANCON0bits.ANSEL1
#define channel_AN1_SetHigh()            do { LATAbits.LATA1 = 1; } while(0)
#define channel_AN1_SetLow()             do { LATAbits.LATA1 = 0; } while(0)
#define channel_AN1_Toggle()             do { LATAbits.LATA1 = ~LATAbits.LATA1; } while(0)
#define channel_AN1_GetValue()           PORTAbits.RA1
#define channel_AN1_SetDigitalInput()    do { TRISAbits.TRISA1 = 1; } while(0)
#define channel_AN1_SetDigitalOutput()   do { TRISAbits.TRISA1 = 0; } while(0)
#define channel_AN1_SetAnalogMode()      do { ANCON0bits.ANSEL1 = 1; } while(0)
#define channel_AN1_SetDigitalMode()     do { ANCON0bits.ANSEL1 = 0; } while(0)

// get/set channel_AN2 aliases
#define channel_AN2_TRIS                 TRISAbits.TRISA2
#define channel_AN2_LAT                  LATAbits.LATA2
#define channel_AN2_PORT                 PORTAbits.RA2
#define channel_AN2_ANS                  ANCON0bits.ANSEL2
#define channel_AN2_SetHigh()            do { LATAbits.LATA2 = 1; } while(0)
#define channel_AN2_SetLow()             do { LATAbits.LATA2 = 0; } while(0)
#define channel_AN2_Toggle()             do { LATAbits.LATA2 = ~LATAbits.LATA2; } while(0)
#define channel_AN2_GetValue()           PORTAbits.RA2
#define channel_AN2_SetDigitalInput()    do { TRISAbits.TRISA2 = 1; } while(0)
#define channel_AN2_SetDigitalOutput()   do { TRISAbits.TRISA2 = 0; } while(0)
#define channel_AN2_SetAnalogMode()      do { ANCON0bits.ANSEL2 = 1; } while(0)
#define channel_AN2_SetDigitalMode()     do { ANCON0bits.ANSEL2 = 0; } while(0)

// get/set channel_AN3 aliases
#define channel_AN3_TRIS                 TRISAbits.TRISA3
#define channel_AN3_LAT                  LATAbits.LATA3
#define channel_AN3_PORT                 PORTAbits.RA3
#define channel_AN3_ANS                  ANCON0bits.ANSEL3
#define channel_AN3_SetHigh()            do { LATAbits.LATA3 = 1; } while(0)
#define channel_AN3_SetLow()             do { LATAbits.LATA3 = 0; } while(0)
#define channel_AN3_Toggle()             do { LATAbits.LATA3 = ~LATAbits.LATA3; } while(0)
#define channel_AN3_GetValue()           PORTAbits.RA3
#define channel_AN3_SetDigitalInput()    do { TRISAbits.TRISA3 = 1; } while(0)
#define channel_AN3_SetDigitalOutput()   do { TRISAbits.TRISA3 = 0; } while(0)
#define channel_AN3_SetAnalogMode()      do { ANCON0bits.ANSEL3 = 1; } while(0)
#define channel_AN3_SetDigitalMode()     do { ANCON0bits.ANSEL3 = 0; } while(0)

// get/set RB2 procedures
#define RB2_SetHigh()            do { LATBbits.LATB2 = 1; } while(0)
#define RB2_SetLow()             do { LATBbits.LATB2 = 0; } while(0)
#define RB2_Toggle()             do { LATBbits.LATB2 = ~LATBbits.LATB2; } while(0)
#define RB2_GetValue()              PORTBbits.RB2
#define RB2_SetDigitalInput()    do { TRISBbits.TRISB2 = 1; } while(0)
#define RB2_SetDigitalOutput()   do { TRISBbits.TRISB2 = 0; } while(0)
#define RB2_SetPullup()             do { WPUBbits.WPUB2 = 1; } while(0)
#define RB2_ResetPullup()           do { WPUBbits.WPUB2 = 0; } while(0)

// get/set RB3 procedures
#define RB3_SetHigh()            do { LATBbits.LATB3 = 1; } while(0)
#define RB3_SetLow()             do { LATBbits.LATB3 = 0; } while(0)
#define RB3_Toggle()             do { LATBbits.LATB3 = ~LATBbits.LATB3; } while(0)
#define RB3_GetValue()              PORTBbits.RB3
#define RB3_SetDigitalInput()    do { TRISBbits.TRISB3 = 1; } while(0)
#define RB3_SetDigitalOutput()   do { TRISBbits.TRISB3 = 0; } while(0)
#define RB3_SetPullup()             do { WPUBbits.WPUB3 = 1; } while(0)
#define RB3_ResetPullup()           do { WPUBbits.WPUB3 = 0; } while(0)

// get/set RC6 procedures
#define RC6_SetHigh()            do { LATCbits.LATC6 = 1; } while(0)
#define RC6_SetLow()             do { LATCbits.LATC6 = 0; } while(0)
#define RC6_Toggle()             do { LATCbits.LATC6 = ~LATCbits.LATC6; } while(0)
#define RC6_GetValue()              PORTCbits.RC6
#define RC6_SetDigitalInput()    do { TRISCbits.TRISC6 = 1; } while(0)
#define RC6_SetDigitalOutput()   do { TRISCbits.TRISC6 = 0; } while(0)

// get/set RC7 procedures
#define RC7_SetHigh()            do { LATCbits.LATC7 = 1; } while(0)
#define RC7_SetLow()             do { LATCbits.LATC7 = 0; } while(0)
#define RC7_Toggle()             do { LATCbits.LATC7 = ~LATCbits.LATC7; } while(0)
#define RC7_GetValue()              PORTCbits.RC7
#define RC7_SetDigitalInput()    do { TRISCbits.TRISC7 = 1; } while(0)
#define RC7_SetDigitalOutput()   do { TRISCbits.TRISC7 = 0; } while(0)

/**
   @Param
    none
   @Returns
    none
   @Description
    GPIO and peripheral I/O initialization
   @Example
    PIN_MANAGER_Initialize();
 */
void PIN_MANAGER_Initialize (void);

/**
 * @Param
    none
 * @Returns
    none
 * @Description
    Interrupt on Change Handling routine
 * @Example
    PIN_MANAGER_IOC();
 */
void PIN_MANAGER_IOC(void);



#endif // PIN_MANAGER_H
/**
 End of File
*/

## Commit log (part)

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2026-06-10 the project has been planned.
2026-06-17 the hardware is developing..
